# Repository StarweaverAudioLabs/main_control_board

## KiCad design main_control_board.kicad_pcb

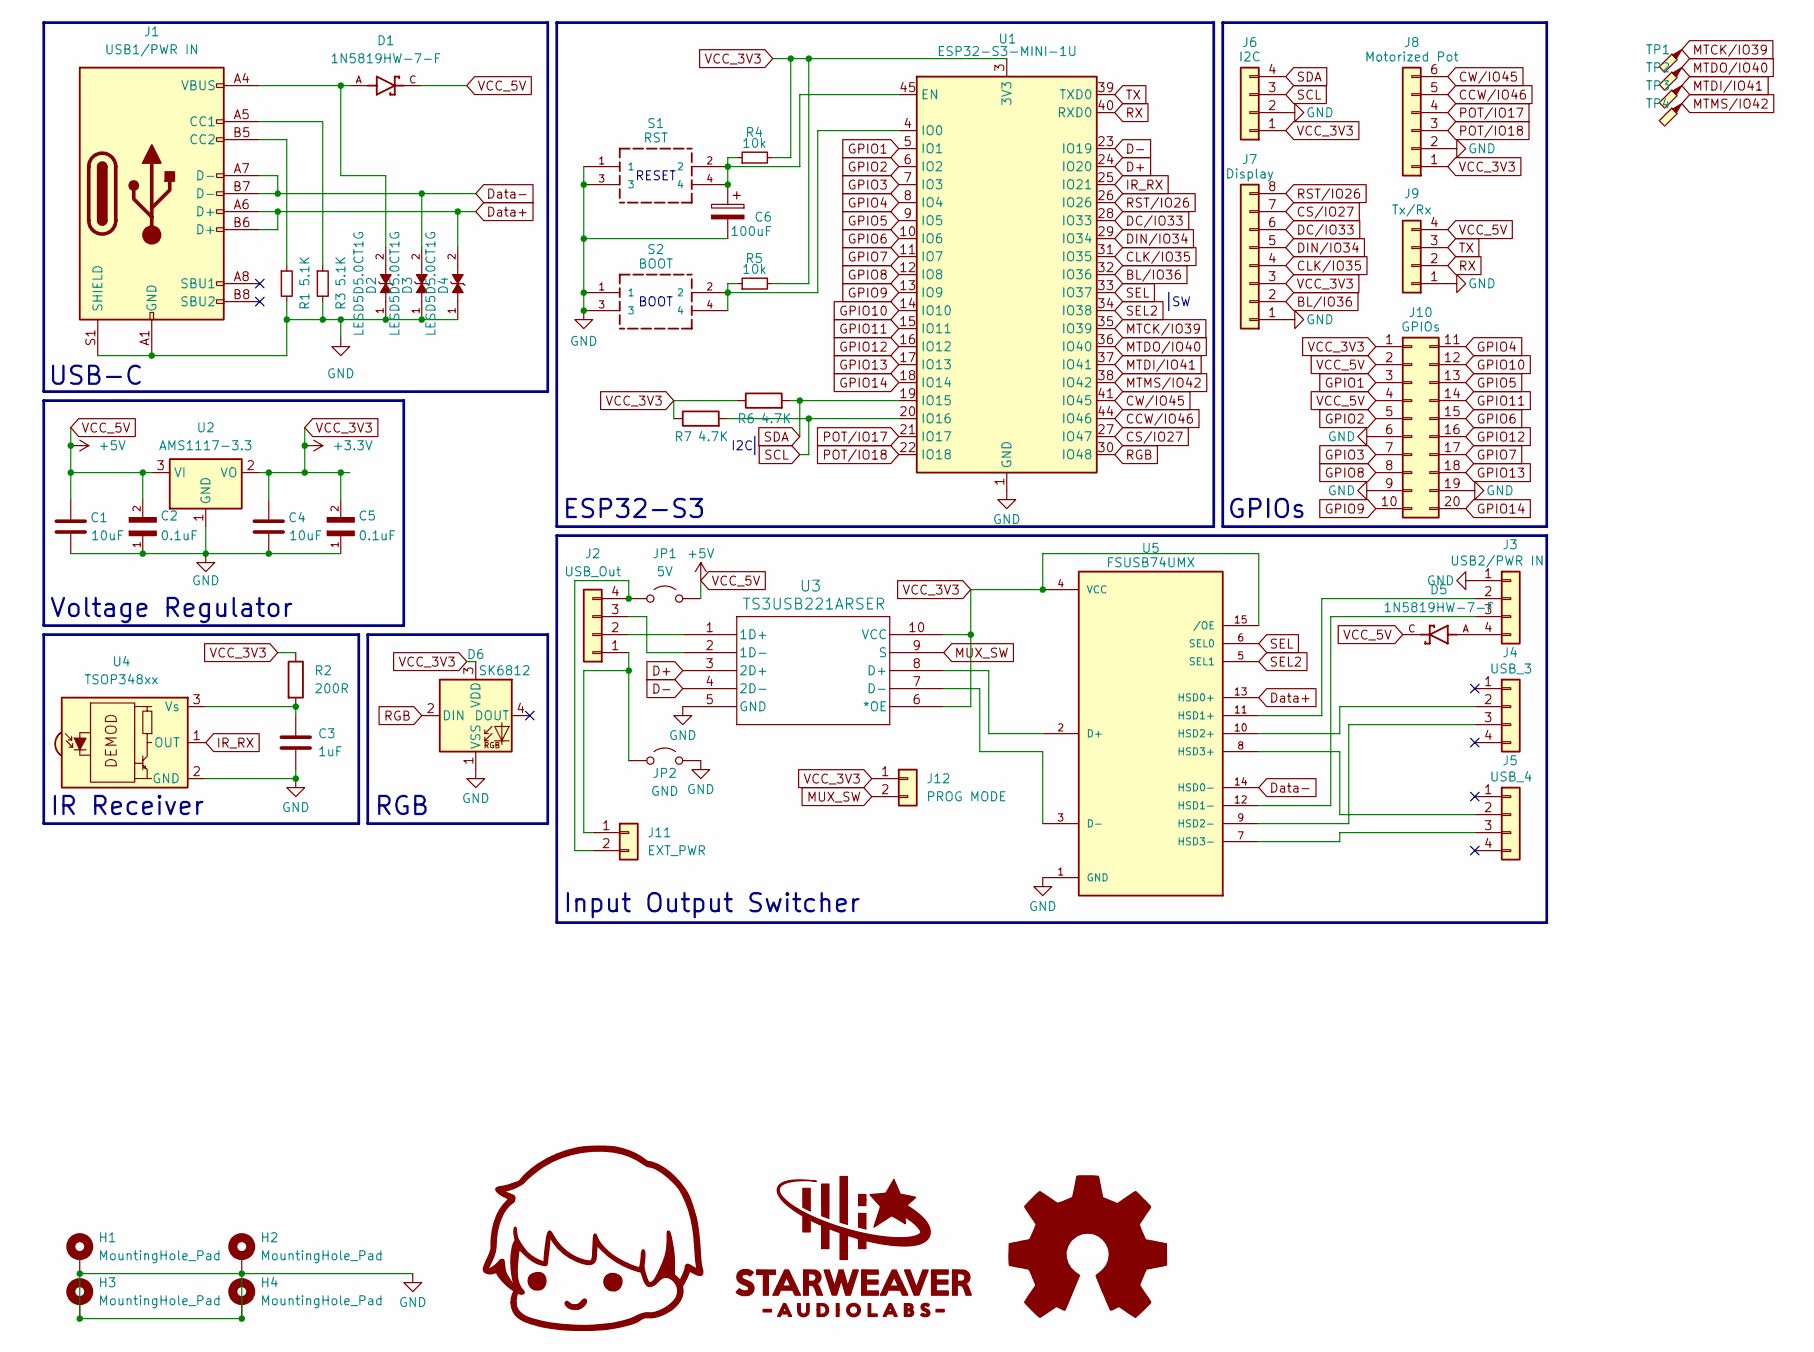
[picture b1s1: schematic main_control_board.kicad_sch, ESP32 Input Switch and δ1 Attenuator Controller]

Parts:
C1, C4: 10uF; C_0805_2012Metric; LCSC C15850
C2, C5: 0.1uF; CAPC1608X90; DigiKey_Part_Number 311-1344-2-ND
C3: 1uF; C_0402_1005Metric; LCSC C52923
C6: 100uF; CP_EIA-3528-21_Kemet-B; LCSC C129289
D1, D5: 1N5819HW-7-F; SOD3715X145N; PARTREV 18-2; LCSC C82544
D2, D3, D4: LESD5D5.0CT1G; TVS_LESD5D5.0CT1G; PARTREV O; LCSC C383211
D6: SK6812; LED_SK6812_PLCC4_5.0x5.0mm_P3.2mm; LCSC C5378720
H1, H2, H3, H4: MountingHole_Pad; MountingHole_2.5mm_Pad
J1: USB1/PWR IN; USB_C_Receptacle_HRO_TYPE-C-31-M-12; LCSC C165948
J2: USB_Out; JST_XH_B4B-XH-A_1x04_P2.50mm_Vertical
J3: USB2/PWR IN; JST_XH_B4B-XH-A_1x04_P2.50mm_Vertical
J4: USB_3; JST_XH_B4B-XH-A_1x04_P2.50mm_Vertical
J5: USB_4; JST_XH_B4B-XH-A_1x04_P2.50mm_Vertical
J6: I2C; PinHeader_1x04_P2.54mm_Vertical
J7: Display; PinSocket_1x08_P2.54mm_Vertical
J8: Motorized Pot; PinHeader_1x06_P2.54mm_Vertical
J9: Tx/Rx; PinHeader_1x04_P2.54mm_Vertical
J10: GPIOs; PinHeader_2x10_P2.54mm_Vertical
J11: EXT_PWR; PinHeader_1x02_P2.54mm_Vertical
J12: PROG MODE; JST_XH_B2B-XH-A_1x02_P2.50mm_Vertical
JP1: 5V; SolderJumper-2_P1.3mm_Open_RoundedPad1.0x1.5mm
JP2: GND; SolderJumper-2_P1.3mm_Open_RoundedPad1.0x1.5mm
R1, R3: 5.1K; R_0603_1608Metric; LCSC C23186
R2: 200R; R_0402_1005Metric; MFR Part# 0402WGF2000TCE; LCSC C25087
R4, R5: 10k; R_0603_1608Metric; LCSC C25804
R6, R7: 4.7K; R_0603_1608Metric; LCSC C23162
S1: RST; PTS810SJG250SMTRLFS; Mouser_Part_Number 611-PTS810SJK250SMTR
S2: BOOT; PTS810SJG250SMTRLFS; Mouser_Part_Number 611-PTS810SJK250SMTR
TP1: MTCK/IO39; TestPoint_Pad_D1.0mm
TP2: MTDO/IO40; TestPoint_Pad_D1.0mm
TP3: MTDI/IO41; TestPoint_Pad_D1.0mm
TP4: MTMS/IO42; TestPoint_Pad_D1.0mm
U1: ESP32-S3-MINI-1U; ESP32-S2-MINI-1U; LCSC C2980299
U2: AMS1117-3.3; SOT-223-3_TabPin2; LCSC C6186
U3: TS3USB221ARSER; RSE10; LCSC C128396
U4: TSOP348xx; Vishay_MOLD-3Pin; LCSC C44620
U5: FSUSB74UMX; QFN40P260X180X55-16N; PARTREV 1.0.2; LCSC C457681

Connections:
BL/IO36: J7.2, U1.32 (IO36)
CCW/IO46: J8.5, U1.44 (IO46)
CLK/IO35: J7.4, U1.31 (IO35)
CS/IO47: J7.7, U1.27 (IO47)
CW/IO45: J8.6, U1.41 (IO45)
D+: U1.24 (IO20), U3.3 (2D+)
D-: U1.23 (IO19), U3.4 (2D-)
DC/IO33: J7.6, U1.28 (IO33)
DIN/IO34: J7.5, U1.29 (IO34)
Data+: D4.2, J1.A6 (D+), J1.B6 (D+), U5.13 (HSD0+)
Data-: D3.2, J1.A7 (D-), J1.B7 (D-), U5.14 (HSD0-)
GND: C1.2, C2.1, C3.2, C4.2, C5.1, C6.2, D2.1, D3.1, D4.1, D6.1 (VSS), H1.1, H2.1, H3.1, H4.1, J1.A1 (GND), J1.A12 (GND), J1.B1 (GND), J1.B12 (GND), J1.S1 (SHIELD), J3.1, J6.2, J7.1, J8.2, J9.1, J10.6, J10.9, J10.19, JP2.2 (B), R1.2, R3.2, S1.1, S1.3, S2.1, S2.3, U1.1 (GND), U1.2 (GND), U1.42 (GND), U1.43 (GND), U1.46 (GND), U1.47 (GND), U1.48 (GND), U1.49 (GND), U1.50 (GND), U1.51 (GND), U1.52 (GND), U1.53 (GND), U1.54 (GND), U1.55 (GND), U1.56 (GND), U1.57 (GND), U1.58 (GND), U1.59 (GND), U1.60 (GND), U1.61 (GND), U1.62 (GND), U1.63 (GND), U1.64 (GND), U1.65 (GND), U2.1 (GND), U3.5 (GND), U4.2 (GND), U5.1 (GND)
GPIO1: J10.3, U1.5 (IO1)
GPIO2: J10.5, U1.6 (IO2)
GPIO3: J10.7, U1.7 (IO3)
GPIO4: J10.11, U1.8 (IO4)
GPIO5: J10.13, U1.9 (IO5)
GPIO6: J10.15, U1.10 (IO6)
GPIO7: J10.17, U1.11 (IO7)
GPIO8: J10.8, U1.12 (IO8)
GPIO9: J10.10, U1.13 (IO9)
GPIO10: J10.12, U1.14 (IO10)
GPIO11: J10.14, U1.15 (IO11)
GPIO12: J10.16, U1.16 (IO12)
GPIO13: J10.18, U1.17 (IO13)
GPIO14: J10.20, U1.18 (IO14)
IR_RX: U1.25 (IO21), U4.1 (OUT)
MTCK/IO39: TP1.1, U1.35 (IO39)
MTDI/IO41: TP3.1, U1.37 (IO41)
MTDO/IO40: TP2.1, U1.36 (IO40)
MTMS/IO42: TP4.1, U1.38 (IO42)
MUX_SW: J12.2, U3.9 (S)
unnamed: D1.A, D2.2, J1.A4 (VBUS), J1.A9 (VBUS), J1.B4 (VBUS), J1.B9 (VBUS)
unnamed: J1.A5 (CC1), R3.1
unnamed: J1.B5 (CC2), R1.1
unnamed: J2.2, U3.1 (1D+)
unnamed: J2.3, U3.2 (1D-)
unnamed: J3.2, U5.11 (HSD1+)
unnamed: J3.3, U5.12 (HSD1-)
unnamed: D5.A, J3.4
unnamed: J4.2, U5.10 (HSD2+)
unnamed: J4.3, U5.9 (HSD2-)
unnamed: J5.2, U5.8 (HSD3+)
unnamed: J5.3, U5.7 (HSD3-)
unnamed: J2.1, J11.1, JP2.1 (A)
unnamed: J2.4, J11.2, JP1.1 (A)
unnamed: C6.1, R4.1, S1.2, S1.4, U1.45 (EN)
unnamed: R5.1, S2.2, S2.4, U1.4 (IO0)
unnamed: U3.8 (D+), U5.2 (D+)
unnamed: U3.7 (D-), U5.3 (D-)
unnamed: C3.1, R2.2, U4.3 (Vs)
POT/IO17: J8.4, U1.21 (IO17)
POT/IO18: J8.3, U1.22 (IO18)
RGB: D6.2 (DIN), U1.30 (IO48)
RST/IO26: J7.8, U1.26 (IO26)
RX: J9.2, U1.40 (RXD0)
SCL: J6.3, R7.2, U1.20 (IO16)
SDA: J6.4, R6.2, U1.19 (IO15)
SEL: U1.33 (IO37), U5.6 (SEL0)
SEL2: U1.34 (IO38), U5.5 (SEL1)
TX: J9.3, U1.39 (TXD0)
VCC_3V3: C4.1, C5.2, D6.3 (VDD), J6.1, J7.3, J8.1, J10.1, J12.1, R2.1, R4.2, R5.2, R6.1, R7.1, U1.3 (3V3), U2.2 (VO), U3.6 (*OE), U3.10 (VCC), U5.4 (VCC), U5.15 (/OE)
VCC_5V: C1.1, C2.2, D1.C, D5.C, J9.4, J10.2, J10.4, JP1.2 (B), U2.3 (VI)

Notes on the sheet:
Voltage Regulator
ESP32-S3
USB-C
GPIOs
BOOT
IR Receiver
RGB
Input Output Switcher
RESET
I2C

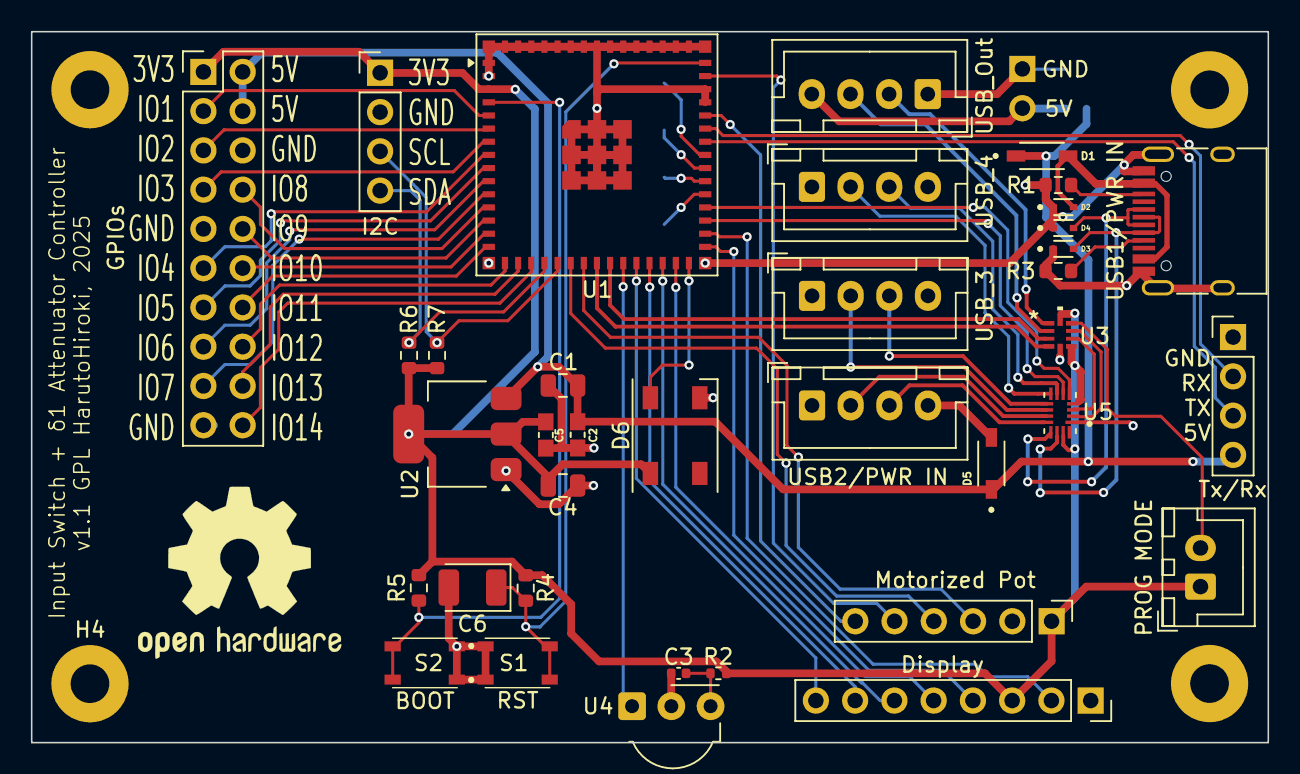
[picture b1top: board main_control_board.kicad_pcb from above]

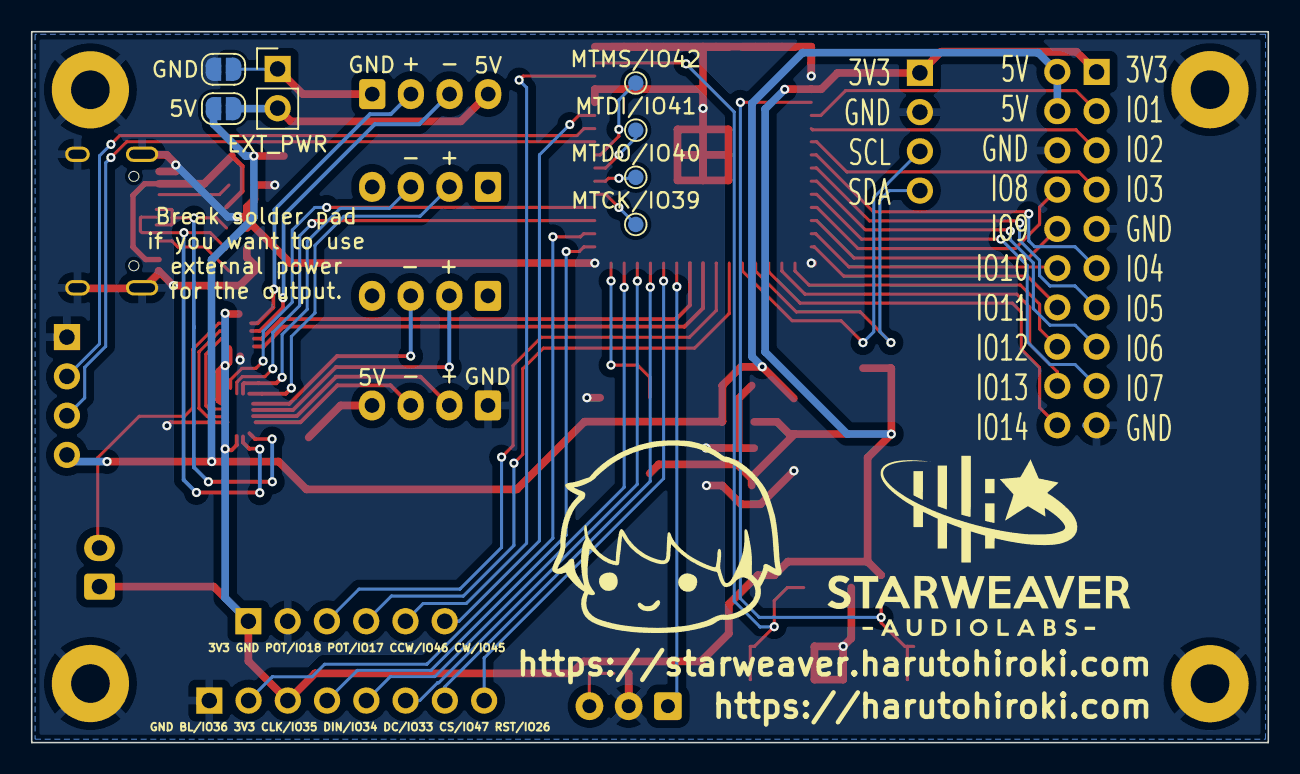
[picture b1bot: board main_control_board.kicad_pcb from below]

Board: 2 copper layers, 80.0 x 46.0 mm, 48 parts (7 on the bottom side), 63 nets.

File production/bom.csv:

Designator,Footprint,Quantity,Value,LCSC Part #
"C1, C4",0805,2,10uF,C15850
"C2, C5",CAPC1608X90,2,0.1uF,C14663
C3,0402,1,1uF,C52923
C6,CP_EIA-3528-21_Kemet-B,1,100uF,C129289
"D1, D5",SOD3715X145N,2,1N5819HW-7-F,C82544
"D2, D3, D4",TVS_LESD5D5.0CT1G,3,LESD5D5.0CT1G,C383211 
D6,LED_SK6812_PLCC4_5.0x5.0mm_P3.2mm,1,SK6812,C5378720
J1,USB_C_Receptacle_HRO_TYPE-C-31-M-12,1,USB1/PWR IN,C165948
J10,PinHeader_2x10_P2.54mm_Vertical,1,GPIOs,
J11,PinHeader_1x02_P2.54mm_Vertical,1,EXT_PWR,
J12,JST_XH_B2B-XH-A_1x02_P2.50mm_Vertical,1,PROG MODE,
J2,JST_XH_B4B-XH-A_1x04_P2.50mm_Vertical,1,USB_Out,
J3,JST_XH_B4B-XH-A_1x04_P2.50mm_Vertical,1,USB2/PWR IN,
J4,JST_XH_B4B-XH-A_1x04_P2.50mm_Vertical,1,USB_3,
J5,JST_XH_B4B-XH-A_1x04_P2.50mm_Vertical,1,USB_4,
J6,PinHeader_1x04_P2.54mm_Vertical,1,I2C,
J7,PinSocket_1x08_P2.54mm_Vertical,1,Display,
J8,PinHeader_1x06_P2.54mm_Vertical,1,Motorized Pot,
J9,PinHeader_1x04_P2.54mm_Vertical,1,Tx/Rx,
JP1,SolderJumper-2_P1.3mm_Open_RoundedPad1.0x1.5mm,1,5V,
JP2,SolderJumper-2_P1.3mm_Open_RoundedPad1.0x1.5mm,1,GND,
"R1, R3",0603,2,5.1K,C23186
R2,0402,1,200R,C25087
"R4, R5",0603,2,10k,C25804
"R6, R7",0603,2,4.7K,C23162
S1,PTS810SJG250SMTRLFS,1,RST,C221896
S2,PTS810SJG250SMTRLFS,1,BOOT,C221896
TP1,TestPoint_Pad_D1.0mm,1,MTCK/IO39,
TP2,TestPoint_Pad_D1.0mm,1,MTDO/IO40,
TP3,TestPoint_Pad_D1.0mm,1,MTDI/IO41,
TP4,TestPoint_Pad_D1.0mm,1,MTMS/IO42,
U1,ESP32-S2-MINI-1U,1,ESP32-S3-MINI-1U,C2980299
U2,SOT-223-3_TabPin2,1,AMS1117-3.3,C6186
U3,RSE10,1,TS3USB221ARSER,C128396
U4,Vishay_MOLD-3Pin,1,TSOP348xx,C44620
U5,QFN40P260X180X55-16N,1,FSUSB74UMX,C457681

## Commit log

2025-05-15 update to latest
2025-05-15 move lib out

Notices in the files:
main_control_board.kicad_pcb:
v1.1 GPL HarutoHiroki, 2025
